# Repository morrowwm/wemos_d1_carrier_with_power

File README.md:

# wemos_d1_carrier_with_power
Wemos D1 Mini carrier board with power DC volt output and I2C interface

This is a simple board takes input up to ~30 VDC and powers a [Wemos D1 Mini](https://universal-solder.ca/product/wemos-d1-mini-esp8266-wifi-iot-module/).
The Wemos D1 controls a MOSFET which switches the input voltage, and has I2C broken out to a 4 pin header. 

Useful for anything which senses the environment and controls something that requires more power of voltage than the D1's ESP8266 can provide. I used it to control a dough proofing oven.

A dough proofing oven controller. Temperature and humidity sensed using an AOSONG AHT25. The MOSFET controls some silicon heating pads.

# Instructions to build
1. In both the Visual Code dough proofer include directory and the Arduino IDE heatbox source folder, there is a secrets.h file. Edit it to set WLAN_SSID1 and WLAN_PASS1 to match your wi-fi credentials. If you are using MQTT, you might want to adjust the three #defines just below to suit your setup. Also the mqtt_server variable further down.
2. What libraries you require depend on the sensors you attach.
3. On the hardware side, the 4-pin header marked J4 has D1, D2, 3V3  and GND connections, moving left to right with the edge closest to J4 facing you.

# Use
1. Before developing with the Wemos D1 connected to your computer via USB, make sure the jumper header marked J2 is __disconnected__. This will ensure you can't power the device from both the external power jack and your computer. Doing so will destroy at least the voltage regulator and possibly the Wemos D1 and your computer.
2. The code contains the ability to do OTA programming.

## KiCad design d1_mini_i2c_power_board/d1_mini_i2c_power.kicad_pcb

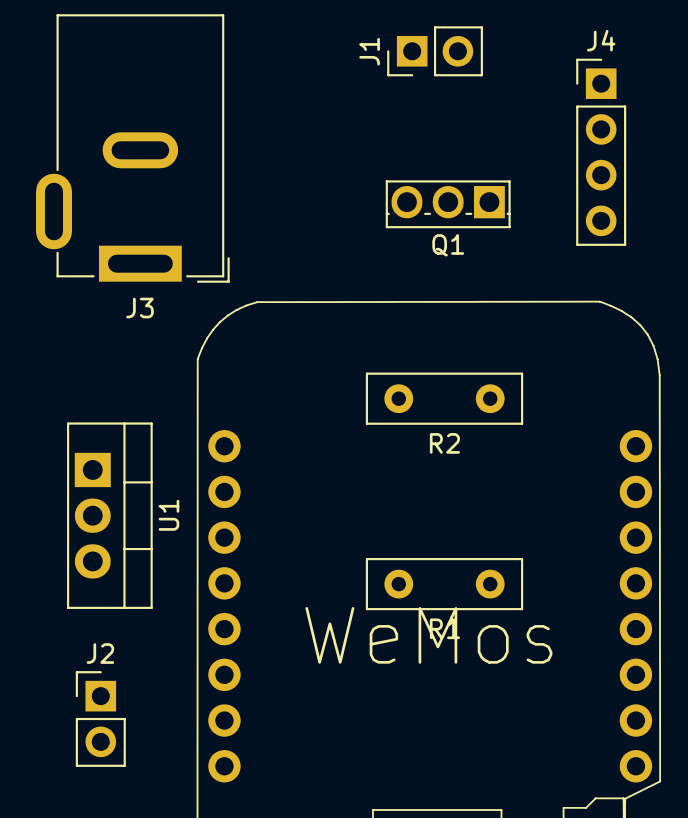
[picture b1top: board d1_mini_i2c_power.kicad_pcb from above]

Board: 2 copper layers, 9 parts (0 on the bottom side), 10 nets, no tracks yet.

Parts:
J1: OUT; PinHeader_1x02_P2.54mm_Vertical
J2: Conn_01x02_Female; PinHeader_1x02_P2.54mm_Vertical
J3: Barrel_Jack; BarrelJack_GCT_DCJ200-10-A_Horizontal
J4: I2C; PinHeader_1x04_P2.54mm_Vertical
Q1: IRLU024NPBF; TO-251-3_Vertical
R1: 690; R_Box_L8.4mm_W2.5mm_P5.08mm
R2: 100K; R_Box_L8.4mm_W2.5mm_P5.08mm
U1: L7805; TO-220-3_Vertical
U2: WeMos_mini; D1_mini_board

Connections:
+3.3V: J4.2, U2.16 (3.3V)
+5V: J2.2, U2.1 (5V)
+12V: J1.1, J3.1, U1.1 (IN)
GND: J3.2, J4.1, Q1.3 (S), R2.2, U1.2 (GND), U2.2 (GND)
unnamed: J1.2, Q1.2 (D)
unnamed: J2.1, U1.3 (OUT)
unnamed: Q1.1 (G), R1.2, R2.1
unnamed: R1.1, U2.15 (D8)
unnamed: J4.3, U2.5 (D2)
unnamed: J4.4, U2.6 (D1)

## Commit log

2023-11-24 added source for dough proofer
2023-11-24 added KiCad files
2023-11-24 image of finished product
2023-11-29 Add source code via upload
